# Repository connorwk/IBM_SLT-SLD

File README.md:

# IBM_SLT-SLD
IBM SLT/SLD reproduced in KiCad

Information obtained from here:
[http://www.bitsavers.org/pdf/ibm/logic/2-6201-H1_SLT_SLD_Module_Data_Dec1969.pdf](http://www.bitsavers.org/pdf/ibm/logic/2-6201-H1_SLT_SLD_Module_Data_Dec1969.pdf)

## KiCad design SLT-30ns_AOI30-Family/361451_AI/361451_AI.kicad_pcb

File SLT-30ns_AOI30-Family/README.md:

# SLT - 30ns (AOI<sub>30</sub> Family) 
[Fact Sheet](http://www.bitsavers.org/pdf/ibm/logic/2-6201-H1_SLT_SLD_Module_Data_Dec1969.pdf#page=28)

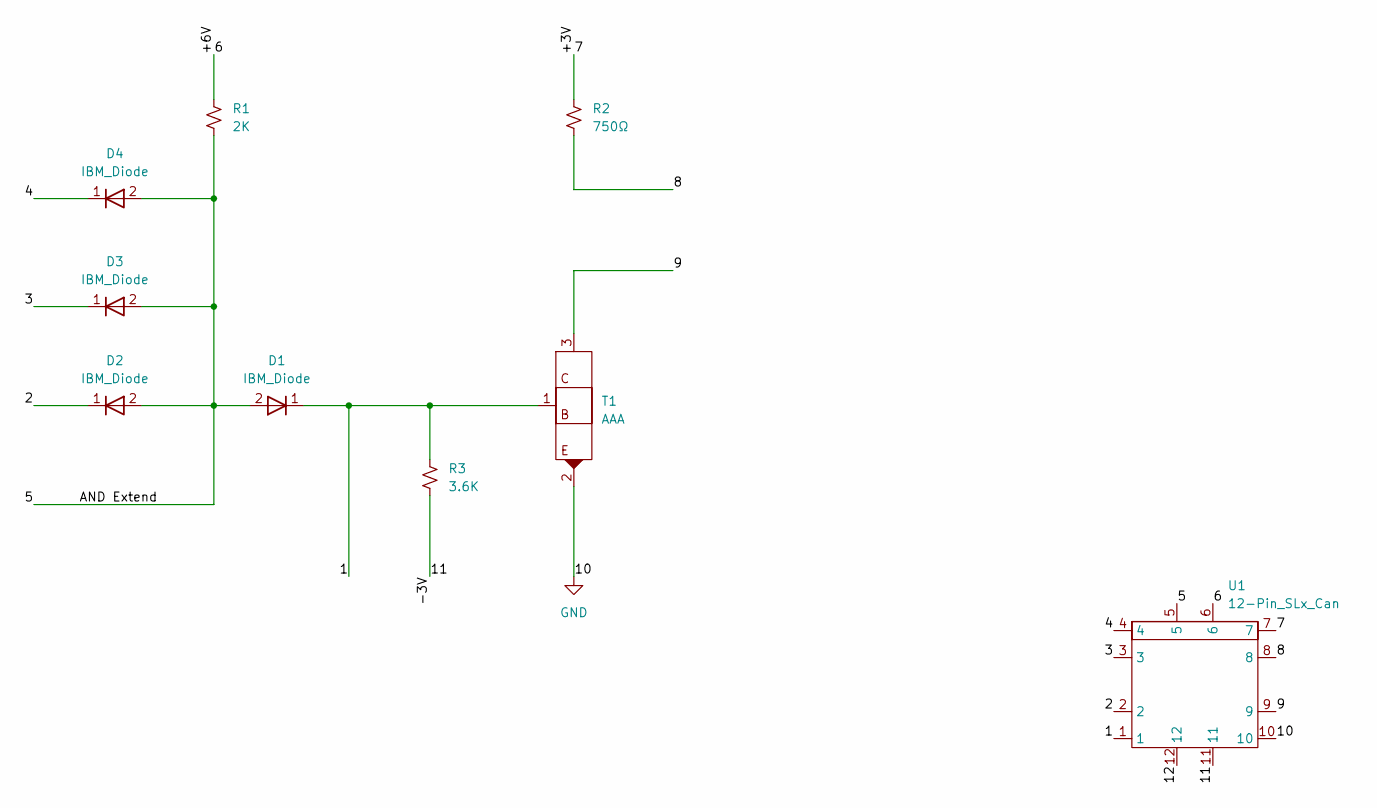
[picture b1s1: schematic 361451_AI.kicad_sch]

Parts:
D1, D2, D3, D4: IBM_Diode; D_0201_0603Metric
R1: 2K; R_0201_0603Metric
R2: 750Ω; R_0201_0603Metric
R3: 3.6K; R_0201_0603Metric
T1: AAA; SOT-883
U1: 12-Pin_SLx_Can

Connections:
/1: D1.1 (K), R3.1, T1.1 (B), U1.1
/2: D2.1 (K), U1.2
/3: D3.1 (K), U1.3
/4: D4.1 (K), U1.4
/5: D1.2 (A), D2.2 (A), D3.2 (A), D4.2 (A), R1.2, U1.5
/8: R2.2, U1.8
/9: T1.3 (C), U1.9
/12: U1.12
/+3V: R2.1, U1.7
/+6V: R1.1, U1.6
/-3V: R3.2, U1.11
GND: T1.2 (E), U1.10

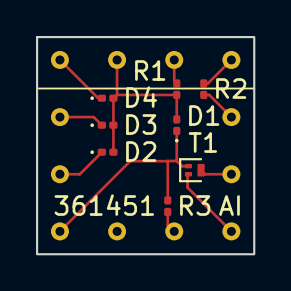
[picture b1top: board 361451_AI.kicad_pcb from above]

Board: 2 copper layers, 12.1 x 12.1 mm, 9 parts (0 on the bottom side), 11 nets.

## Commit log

2022-02-19 Update gitignore
2022-02-19 Initial directories creation, and 361408 AOI11
2022-02-19 Correction to READMEs
2022-02-19 Correction to 361408 README
2022-02-20 Initial schematics for 361409, 361410, 361412
2022-02-20 Add schematics for 361413, 361414
2022-02-22 361447 schematic
2022-02-22 Updated schematics
2022-02-22 Bunch of schematics.
2022-08-04 Finished off the SLT-30 family of parts, started on the SLT-700 family. Changed labeling of transistors and diodes in all schematics, but have yet to update all the pdf files. This is a TODO...
2022-08-09 Finished off all schematics for SLT familys. Still need to export all pdfs and finish PCBs.
2022-12-29 Updates to 361451 AI.
2023-02-05 Added labels for set/reset and +/- outputs
2023-02-05 Update schematic pdfs
2023-02-06 Add can P/N to schematics for SLT-700
2023-02-19 Starting on Passives, this is going to just be necessary at this point for REing efforts.
2023-02-19 Believe the 2391124 is an inductor. Measures as just over an Ohm...
